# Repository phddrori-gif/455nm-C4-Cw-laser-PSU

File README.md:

# 455 nm 151 W Laser Array

## Overview
This repository documents the design, assembly, and testing of a 455 nm, 151 W diode laser array system built for high-power laser experimentation and materials research. The project combines optical, electrical, thermal, and safety engineering to create a controlled platform for evaluating laser performance and exploring laser-heated crystal growth.

## Project Objectives
- Achieve the full 151 W output of the diode array
- Explore laser-based growth of synthetic ruby
- Evaluate whether the system can be adapted for additional materials, including sapphire

## Current Status
The laser platform is operational in several core areas, with major progress completed in the safety, electrical, and mechanical subsystems. Remaining work is focused on characterization, documentation, and material-processing experiments.

## Safety Systems
Because this project involves a high-power 455 nm laser source, safety controls were treated as a primary design requirement.

Implemented safety features:
- OD8+ laser safety eyewear rated for 455 nm
- Hall-effect current sensing with ESP32-based monitoring
- Temperature-based automatic shutdown
- Emergency stop (E-stop)

## Mechanical and System Assembly
Completed design and integration work includes:
- 3D CAD model for the laser and circuit assembly
- Circuit design and schematic development
- PCB layout
- Custom lens holder
- Hybrid cooling system using both water cooling and forced-air cooling

## Electrical and Control Design
Completed electrical work:
- Tested PWM control and mechanical switch logic
- Verified full-wave rectifier suitability for 120 V AC input
- Integrated an IRM-05-3.3 power supply for the Teensy 4.0 controller
- Selected a 5.6 kOhm thermistor reference resistor based on a maximum expected operating temperature of 75 C

In progress:
- Fully label and reorganize the circuit diagram into clearly separated functional blocks

## Optical and Thermal Work
Completed:
- Selected a candidate focal length for the lens system (approximately +30 cm)

In progress:
- Determine the diode array's maximum allowable thermal load
- Measure and verify the optical power output of the diode array

## Materials and Crystal Growth Experiments
Completed:
- Acquired crucible for high-temperature material tests
- Acquired aluminum powder and chromium oxide for ruby experiments
- Planned work to be conducted in a fume hood

Planned:
- Acquire aluminum powder and iron oxide for sapphire experiments
- Evaluate the addition of titanium oxide for blue sapphire trials

## Next Steps
- Complete final circuit documentation
- Characterize thermal limits of the diode array
- Measure output power under controlled operating conditions
- Begin laser-heated ruby growth experiments
- Expand testing to additional materials if ruby trials are successful

## Resume Highlights
This project demonstrates experience in:
- High-power laser system integration
- Embedded monitoring and safety interlocks
- PCB and circuit design
- Thermal management
- Experimental hardware development
- Applied materials research

## Disclaimer
This repository documents work involving high-power laser equipment and high-temperature material processing. Testing should only be performed with proper protective equipment, controlled procedures, and appropriate lab safety infrastructure.

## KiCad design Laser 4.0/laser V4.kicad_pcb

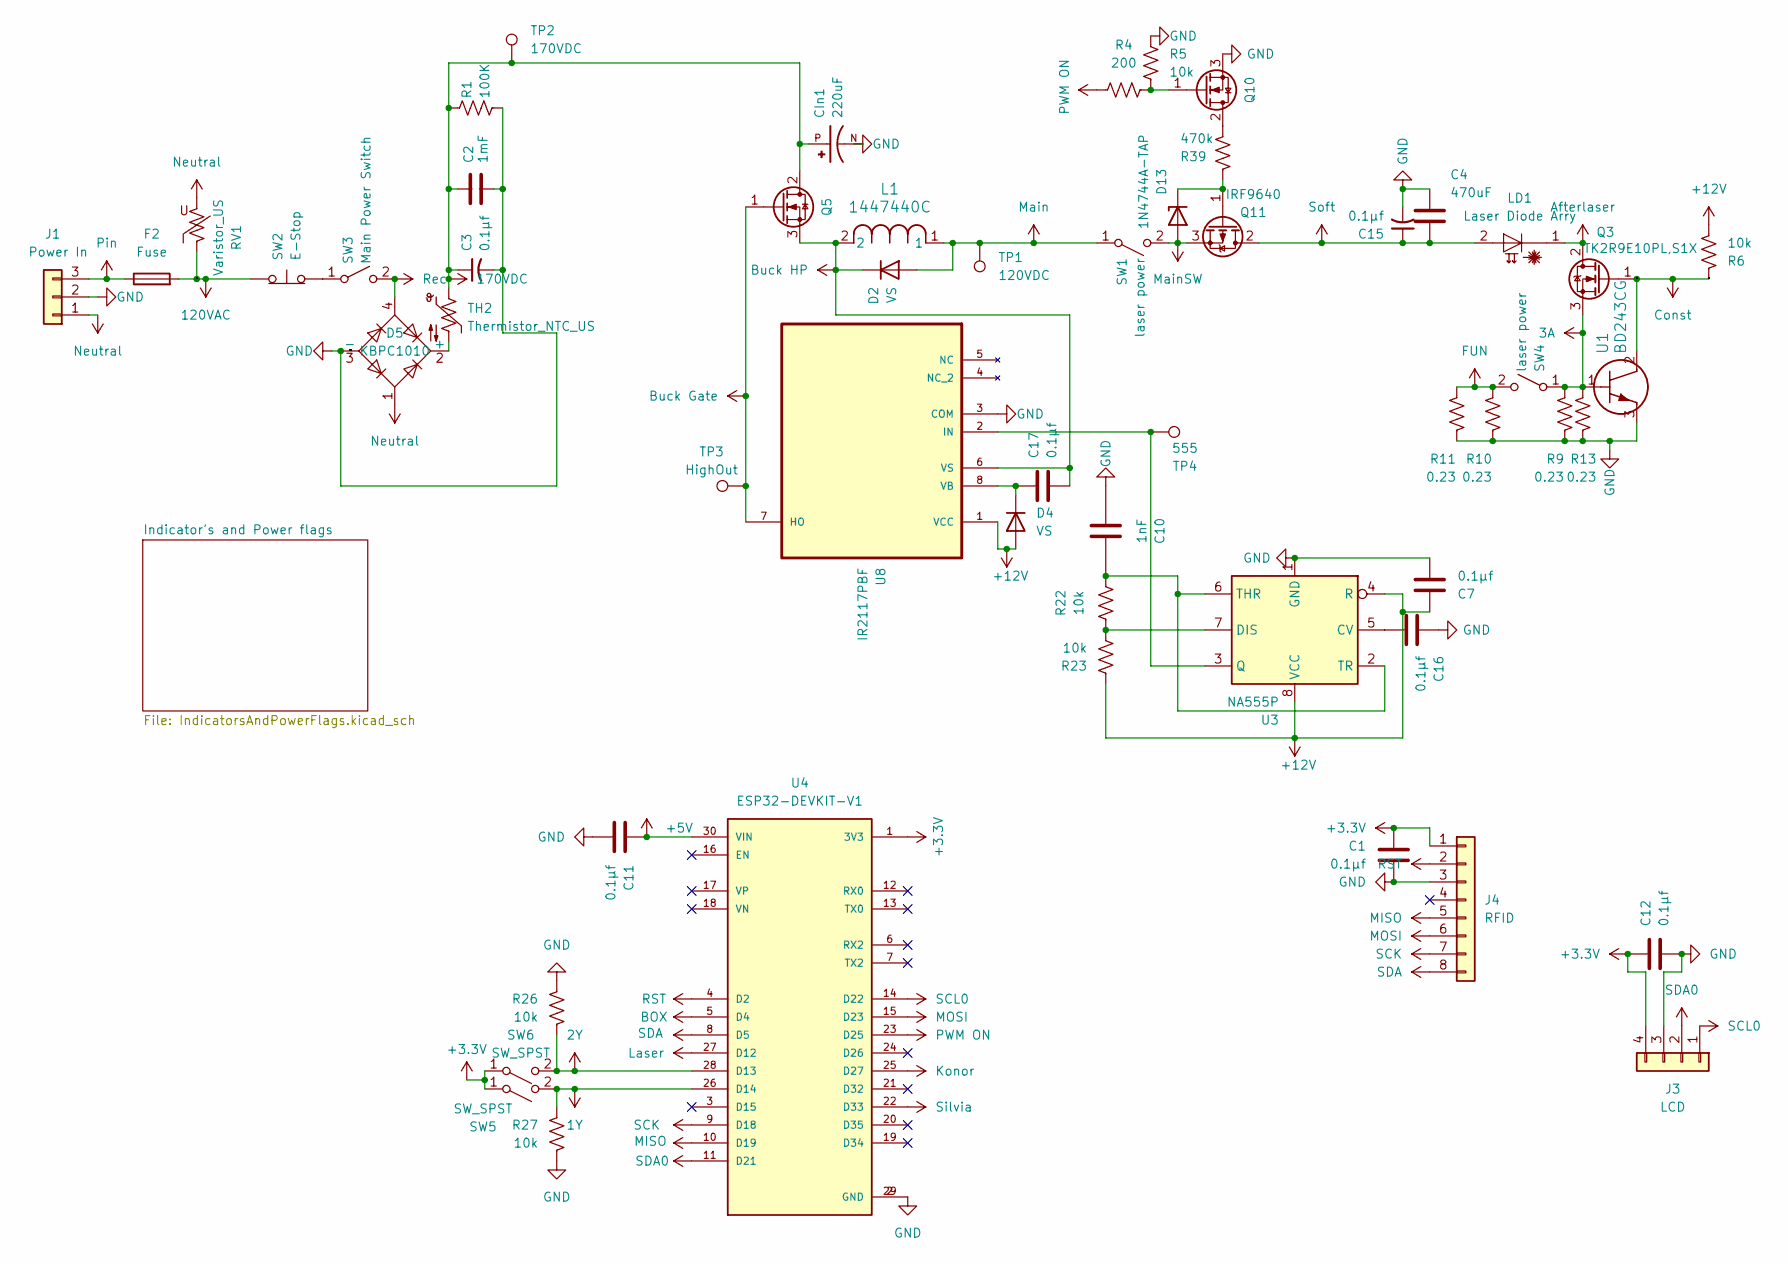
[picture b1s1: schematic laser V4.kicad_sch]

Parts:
C1, C7, C11, C12, C16, C17: 0.1µf; CP_Radial_D4.0mm_P2.00mm; Digikey 399-C320C104K5R5TA7305CT-ND
C2: 1mF; CP_Radial_D35.0mm_P10.00mm_SnapIn; Digikey 493-8541-ND
C3, C15: 0.1µf; CP_Radial_D4.0mm_P2.00mm; Digikey 399-3508-ND
C4: 470uF; CAPPRD500W60D1000H3150; Digikey 565-2971-ND
C10: 1nF; CP_Radial_D4.0mm_P2.00mm; Digikey 56-K102K15X7RF53H5G-ND
CIn1: 220uF; CAPPRD750W80D1600H3150; PARTREV 28-FEB-20; Digikey P13529-ND
D2, D4: VS; TO-220-2_Vertical; Digikey VS-HFA04TB60-M3GI-ND
D5: KBPC1010; Digikey 5272-KBPC1010-ND
D13: 1N4744A-TAP; D_DO-41_SOD81_P10.16mm_Horizontal; Digikey 1N4744A-TAPGICT-ND
F2: Fuse; Fuseholder_Clip-5x20mm_Littelfuse_100_Inline_P20.50x4.60mm_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; Digikey 486-4875-ND
J1: Power In; C14_thru hole
J3: LCD; FanPinHeader_1x04_P2.54mm_Vertical
J4: RFID; PinSocket_1x08_P2.54mm_Vertical
L1: 1447440C; 1447440C_MUR; Digikey 811-1332-ND
LD1: Laser Diode Arry; NUBM3D_LaserDiode_Pads
Q3: TK2R9E10PL,S1X; TO-220-3_Horizontal_TabUp; Digikey 264-TK2R9E10PL,S1X-ND
Q5, Q10: SIHP33N60E-GE3; TO-220-3_Horizontal_TabUp; Digikey 742-SIHP33N60E-GE3-ND
Q11: IRF9640; TO-220-3_Horizontal_TabUp; Digikey 742-IRF9640PBF-BE3-ND
R1: 100K; R_Axial_DIN0411_L9.9mm_D3.6mm_P12.70mm_Horizontal; Digikey A131429CT-ND
R4: 200; R_Axial_DIN0207_L6.3mm_D2.5mm_P10.16mm_Horizontal; Digikey RNF14FTD200RTR-ND
R5, R6, R22, R26, R27: 10k; R_Axial_DIN0207_L6.3mm_D2.5mm_P10.16mm_Horizontal; Digikey CF14JT10K0TR-ND
R9, R10, R11, R13: 0.23; R_Axial_Power_L20.0mm_W6.4mm_P25.40mm; Digikey A137272CT-ND
R23: 10k; R_Axial_DIN0207_L6.3mm_D2.5mm_P10.16mm_Horizontal; Digikey S3.3KQTR-ND
R39: 470k; R_Axial_DIN0207_L6.3mm_D2.5mm_P10.16mm_Horizontal
RV1: Varistor_US; VARRB750W81L1700T500H2250; DigiKey F4008-ND
SW1, SW4: laser power; TerminalBlock_WAGO_236-402_1x02_P5.00mm_45Degree; Digikey 708-3049-ND
SW2: E-Stop; TerminalBlock_WAGO_236-402_1x02_P5.00mm_45Degree
SW3: Main Power Switch; TerminalBlock_WAGO_236-402_1x02_P5.00mm_45Degree; Digikey 708-3049-ND
SW5, SW6: SW_SPST; PinHeader_1x02_P2.54mm_Vertical
TH2: Thermistor_NTC_US; RV_Disc_D21.5mm_W7.5mm_P10mm; Digikey 570-MS3220010-ND
TP1: 120VDC; TestPoint_Plated_Hole_D2.0mm
TP2: 170VDC; TestPoint_Plated_Hole_D2.0mm
TP3: HighOut; TestPoint_Plated_Hole_D2.0mm
TP4: 555; TestPoint_Plated_Hole_D2.0mm
U1: BD243CG; TO-220-3_Horizontal_TabUp; Digikey BD243CGOS-ND
U3: NA555P; DIP-8_W7.62mm; Digikey 296-21753-5-ND
U4: ESP32-DEVKIT-V1; MODULE_ESP32_DEVKIT_V1; PARTREV N/A
U8: IR2117PBF; DIP254P762X533-8; MPN IR2117PBF

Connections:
1Y: R27.1, SW5.2 (B), U4.26 (D14); also elsewhere on the board
2Y: R26.2, SW6.2 (B), U4.28 (D13); also elsewhere on the board
3A: Q3.3 (S), R9.1, R13.1, SW4.1 (A), U1.1
120VAC: F2.2, RV1.1, SW2.1 (A)
170VDC: C2.1, C3.1, CIn1.P, D5.2 (+), Q5.2 (D), R1.1, TH2.1, TH2.2, TP2.1; also elsewhere on the board
+3.3V: C1.1, C12.1, J3.4, J4.1, SW5.1 (A), SW6.1 (A), U4.1 (3V3); also elsewhere on the board
+5V: C11.1, U4.30 (VIN); also elsewhere on the board
+12V: C7.1, D4.2 (A), R6.2, R23.1, U3.4 (R), U3.8 (VCC), U8.1 (VCC); also elsewhere on the board
Afterlaser: LD1.1 (C), Q3.2 (D)
BOX: U4.5 (D4)
Buck Gate: Q5.1 (G), TP3.1, U8.7 (HO)
Buck HP: C17.2, D2.1 (K), L1.2, Q5.3 (S), U8.6 (VS)
Const: Q3.1 (G), R6.1, U1.2
FUN: R10.1, R11.1, SW4.2 (B); also elsewhere on the board
GND: C1.2, C2.2, C3.2, C4.1, C7.2, C10.2, C11.2, C12.2, C15.2, C16.1, CIn1.N, D5.3 (-), J1.2, J3.3, J4.3, Q10.3 (S), R1.2, R5.1, R9.2, R10.2, R11.2, R13.2, R26.1, R27.2, U1.3, U3.1 (GND), U4.2 (GND), U4.29 (GND), U8.3 (COM); also elsewhere on the board
Konor: U4.25 (D27); also elsewhere on the board
Laser: U4.27 (D12); also elsewhere on the board
MISO: J4.5, U4.10 (D19)
MOSI: J4.6, U4.15 (D23)
Main: D2.2 (A), L1.1, SW1.1 (A), TP1.1
MainSW: D13.2 (A), Q11.3 (S), SW1.2 (B)
unnamed: C17.1, D4.1 (K), U8.8 (VB)
unnamed: D13.1 (K), Q11.1 (G), R39.1
unnamed: Q10.2 (D), R39.2
unnamed: Q10.1 (G), R4.2, R5.2
unnamed: SW2.2 (B), SW3.1 (A)
unnamed: C16.2, U3.5 (CV)
unnamed: R22.2, R23.2, U3.7 (DIS)
unnamed: TP4.1, U3.3 (Q), U8.2 (IN)
unnamed: C10.1, R22.1, U3.2 (TR), U3.6 (THR)
Neutral: D5.1, J1.1, RV1.2; also elsewhere on the board
PWM ON: R4.1, U4.23 (D25)
Pin: F2.1, J1.3; also elsewhere on the board
RST: J4.2, U4.4 (D2)
Rec: D5.4, SW3.2 (B)
SCK: J4.7, U4.9 (D18)
SCL0: J3.1, U4.14 (D22)
SDA: J4.8, U4.8 (D5)
SDA0: J3.2, U4.11 (D21)
Silvia: U4.22 (D33); also elsewhere on the board
Soft: C4.2, C15.1, LD1.2 (A), Q11.2 (D)

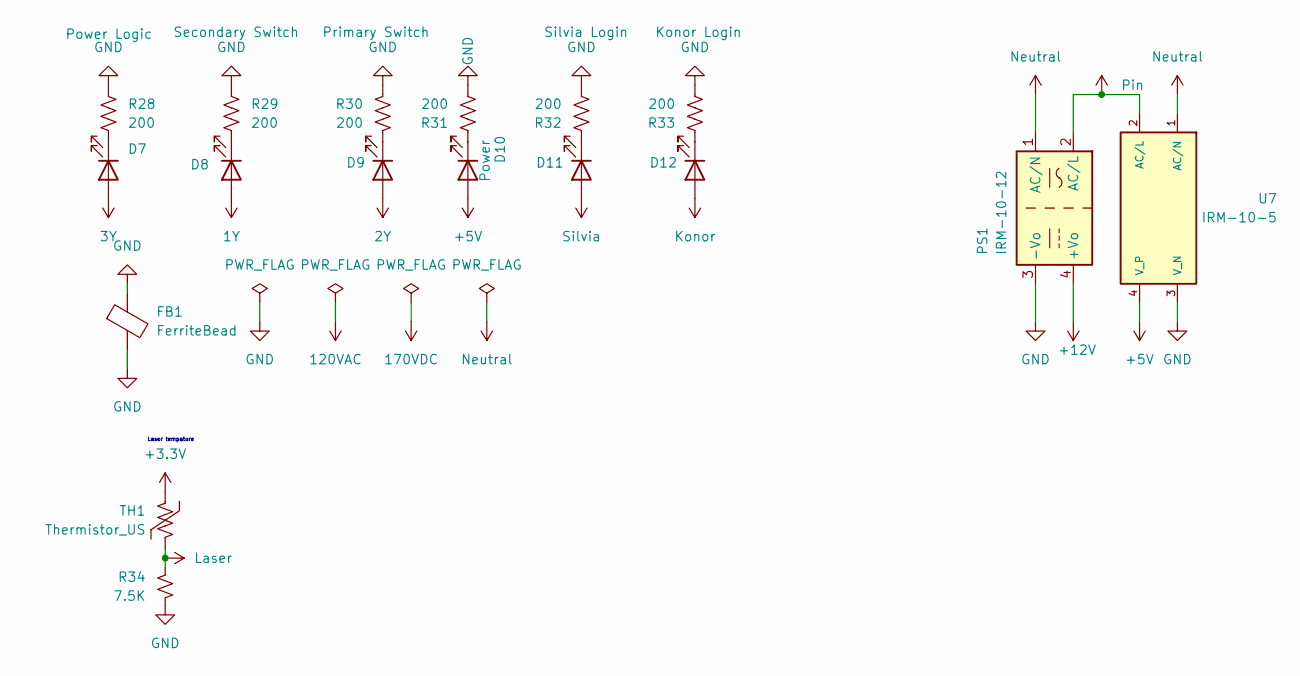
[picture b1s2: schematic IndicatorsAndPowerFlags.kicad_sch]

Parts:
D7: Power Logic; LED_D5.0mm; Digikey 732-5016-ND
D8: Secondary Switch; LED_D5.0mm; Digikey 732-5016-ND
D9: Primary Switch; LED_D5.0mm; Digikey 732-5016-ND
D10: Power; LED_D5.0mm; Digikey 732-5016-ND
D11: Silvia Login; LED_D5.0mm; Digikey 732-5016-ND
D12: Konor Login; LED_D5.0mm; Digikey 732-5016-ND
FB1: FerriteBead; R_Axial_DIN0207_L6.3mm_D2.5mm_P7.62mm_Horizontal; Digikey 1934-1476-2-ND
PS1: IRM-10-12; Converter_ACDC_MeanWell_IRM-10-xx_THT; Digikey 1866-3028-ND
R28, R29, R30, R31, R32, R33: 200; R_Axial_DIN0207_L6.3mm_D2.5mm_P10.16mm_Horizontal; Digikey RNF14FTD200RTR-ND
R34: 7.5K; R_Axial_DIN0207_L6.3mm_D2.5mm_P10.16mm_Horizontal
TH1: Thermistor_US; PinHeader_1x02_P2.54mm_Vertical; Digikey 317-1258-ND
U7: IRM-10-5; CONV_IRM-10-5; Digikey 1866-3032-ND

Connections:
1Y: D8.2 (A); also elsewhere on the board
2Y: D9.2 (A); also elsewhere on the board
3Y: D7.2 (A)
+3.3V: TH1.1; also elsewhere on the board
+5V: D10.2 (A), U7.4 (V_P); also elsewhere on the board
+12V: PS1.4 (+Vo); also elsewhere on the board
GND: FB1.1, FB1.2, PS1.3 (-Vo), R28.1, R29.2, R30.1, R31.2, R32.2, R33.2, R34.1, U7.3 (V_N); also elsewhere on the board
Konor: D12.2 (A); also elsewhere on the board
Laser: R34.2, TH1.2; also elsewhere on the board
unnamed: D7.1 (K), R28.2
unnamed: D8.1 (K), R29.1
unnamed: D9.1 (K), R30.2
unnamed: D10.1 (K), R31.1
unnamed: D11.1 (K), R32.1
unnamed: D12.1 (K), R33.1
Neutral: PS1.1 (AC/N), U7.1 (AC/N); also elsewhere on the board
Pin: PS1.2 (AC/L), U7.2 (AC/L); also elsewhere on the board
Silvia: D11.2 (A); also elsewhere on the board

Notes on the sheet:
Laser tempature

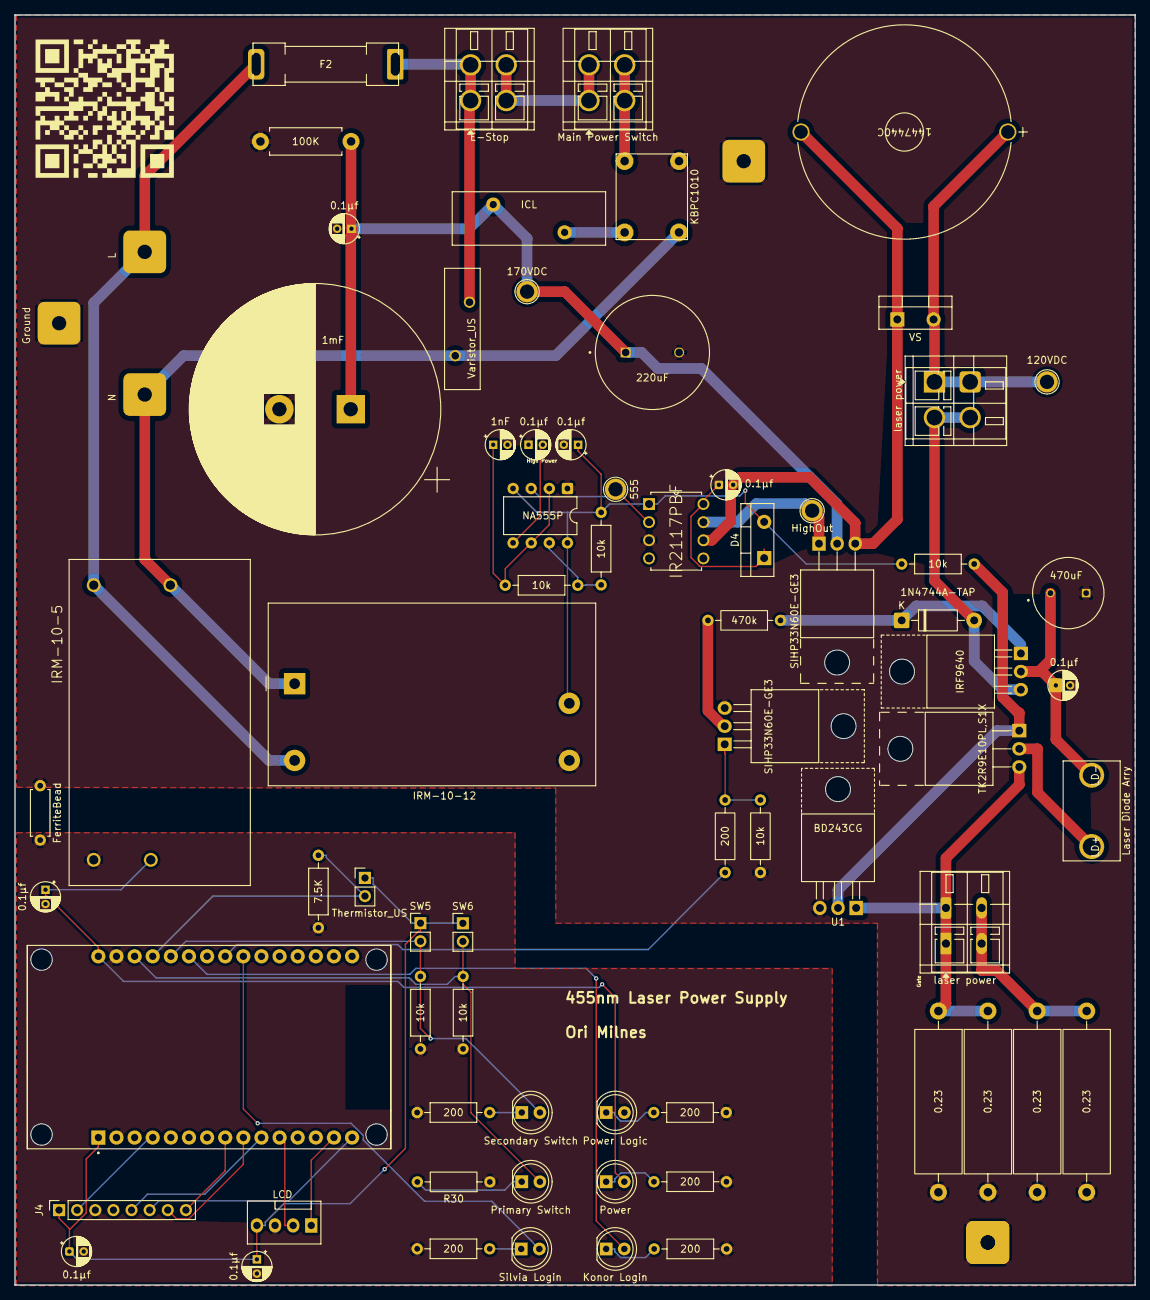
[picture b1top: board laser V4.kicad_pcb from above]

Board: 2 copper layers, 157.0 x 178.0 mm, 73 parts (0 on the bottom side), 46 nets.

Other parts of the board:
0.23, 0.23#2: 0.23; R_Axial_Power_L20.0mm_W6.4mm_P25.40mm
G1: LOGO
ICL: Thermistor_NTC_US; RV_Disc_D21.5mm_W7.5mm_P10mm

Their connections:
170VDC: ICL.1, ICL.2; also elsewhere on the board
FUN: 0.23.1, 0.23#2.1; also elsewhere on the board
GND: 0.23.2, 0.23#2.2; also elsewhere on the board

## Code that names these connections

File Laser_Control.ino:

#include <Wire.h>
#include <SPI.h>
#include <MFRC522.h>
#include <LiquidCrystal_I2C.h>
#include <math.h>
#include <Watchdog_t4.h>

WDT_T4<WDT1> wdt;

// RFID RC522
#define RST_PIN 9
#define SS_PIN 10
MFRC522 mfrc522(SS_PIN, RST_PIN);

// LCD I2C
LiquidCrystal_I2C lcd(0x27, 16, 2);

// Known UIDs
const byte UID_A[] = { 0x73, 0xD6, 0xEE, 0xAE };  // KONOR
const byte UID_B[] = { 0x53, 0x77, 0xAB, 0x98 };  // SILVIA
const byte UID_A_LEN = sizeof(UID_A);
const byte UID_B_LEN = sizeof(UID_B);

// Pins
const int THERMISTOR_LASER_PIN  = A0;  // pin 14
const int THERMISTOR_MOSFET_PIN = A3;  // pin 17
const int VOLTAGE1_PIN   = A1;  // pin 15
const int VOLTAGE2_PIN   = A2;  // pin 16
const int CURRENT_PIN    = A8;  // pin 22
const int PWM_LASER_PIN  = 23;
const int PWM_ON_PIN     = 8;
const int KONOR_LED_PIN  = 6;
const int SILVIA_LED_PIN = 7;

// Constants
const float ADC_REF = 3.3;
const int ADC_RES = 4095;
const float SHUNT_RESISTANCE = 0.1;
const float VOLT_DIV_RATIO_1 = 57.0;
const float VOLT_DIV_RATIO_2 = 37.0;

// System State
bool isA_loggedIn = false;
bool isB_loggedIn = false;
bool isLocked = false;
bool inCooldown = false;
int unknownScanCount = 0;
int pwmLaserValue = 255;  // default 100%

// Override
bool overrideMode = false;
unsigned long overrideStartTime = 0;
const unsigned long overrideDuration = 60000;
unsigned long lastUIDScanTime = 0;
const unsigned long overrideScanWindow = 3000;
byte lastUID[10];
byte lastUIDLen = 0;

// Timing
unsigned long lastVoltageSwitch = 0;
unsigned long lastDisplayUpdate = 0;
unsigned long cooldownStart = 0;
const unsigned long voltageSwitchInterval = 5000;
const unsigned long displayInterval = 200;
const unsigned long cooldownDuration = 60000;
bool showVoltage1 = true;

// Soft start
unsigned long softStartStartTime = 0;
const unsigned long softStartDuration = 5000;  // 5 seconds

void setup() {
  Serial.begin(115200);
  analogReadResolution(12);
  analogReadAveraging(8);
  pinMode(PWM_LASER_PIN, OUTPUT);
  pinMode(PWM_ON_PIN, OUTPUT);
  pinMode(KONOR_LED_PIN, OUTPUT);
  pinMode(SILVIA_LED_PIN, OUTPUT);
  analogWrite(PWM_LASER_PIN, 0);
  analogWrite(PWM_ON_PIN, 0);

  WDT_timings_t config = {
    .trigger = 8000,
    .timeout = 16000,
    .callback = nullptr
  };
  wdt.begin(config);

  lcd.init();
  lcd.backlight();
  lcd.setCursor(0, 0);
  lcd.print("LCD OK...");
  delay(500);

  SPI.begin();
  mfrc522.PCD_Init();
  delay(100);
  lcd.clear();
  lcd.print("RFID Ready");
  delay(1000);
  lcd.clear();
}

void loop() {
  wdt.feed();

  static int lastPwmOnValue = -1;
  static int lastLaserPwmValue = -1;
  static bool lastPwmOn = false;

  digitalWrite(KONOR_LED_PIN, isA_loggedIn);
  digitalWrite(SILVIA_LED_PIN, isB_loggedIn);

  float tempC = readTemperature(THERMISTOR_LASER_PIN);
  if ((tempC >= 60.0 || tempC > 150.0) && !inCooldown) enterCooldown("TEMP ERROR");
  if (inCooldown) { handleCooldown(); return; }

  if (Serial.available()) {
    int input = Serial.parseInt();
    if (input >= 0 && input <= 255) {
      pwmLaserValue = input;
    }
  }

  // RFID logic
  if (mfrc522.PICC_IsNewCardPresent() && mfrc522.PICC_ReadCardSerial()) {
    byte* uid = mfrc522.uid.uidByte;
    byte uidLen = mfrc522.uid.size;
    unsigned long now = millis();

    if (compareUID(uid, uidLen, UID_A, UID_A_LEN)) {
      if (lastUIDLen == UID_A_LEN && compareUID(uid, uidLen, lastUID, lastUIDLen)) {
        if (now - lastUIDScanTime <= overrideScanWindow) {
          overrideMode = true;
          overrideStartTime = now;
          softStartStartTime = now;
          lcd.clear();
          lcd.setCursor(0, 0);
          lcd.print("OVERRIDE MODE");
          delay(1000);
          lcd.clear();
        }
      }
      memcpy(lastUID, uid, uidLen);
      lastUIDLen = uidLen;
      lastUIDScanTime = now;
    }

    if (compareUID(uid, uidLen, UID_A, UID_A_LEN)) {
      isA_loggedIn = !isA_loggedIn;
      unknownScanCount = 0;
    } else if (compareUID(uid, uidLen, UID_B, UID_B_LEN)) {
      if (!isLocked) {
        isB_loggedIn = !isB_loggedIn;
        unknownScanCount = 0;
      }
    } else {
      unknownScanCount++;
      if (unknownScanCount >= 2) {
        isA_loggedIn = false;
        isB_loggedIn = false;
        isLocked = true;
      }
    }

    mfrc522.PICC_HaltA();
  }

  if (overrideMode && millis() - overrideStartTime > overrideDuration) {
    overrideMode = false;
  }

  float currentVoltage = analogRead(CURRENT_PIN) * (ADC_REF / ADC_RES);
  float currentAmps = currentVoltage / SHUNT_RESISTANCE;
  float voltage1 = analogRead(VOLTAGE1_PIN) * (ADC_REF / ADC_RES) * VOLT_DIV_RATIO_1;
  float voltage2 = analogRead(VOLTAGE2_PIN) * (ADC_REF / ADC_RES) * VOLT_DIV_RATIO_2;

  bool pwmOn = ((isA_loggedIn && isB_loggedIn) || overrideMode) && !isLocked;

  // Detect rising edge for soft start
  if (pwmOn && !lastPwmOn) {
    softStartStartTime = millis();
  }
  lastPwmOn = pwmOn;

  // Soft-start PWM (pin 8)
  int pwmOnValue = 0;
  if (pwmOn) {
    unsigned long elapsed = millis() - softStartStartTime;
    pwmOnValue = (elapsed >= softStartDuration) ? 255 : map(elapsed, 0, softStartDuration, 0, 255);
  } else {
    pwmOnValue = 0;
  }
  if (pwmOnValue != lastPwmOnValue) {
    analogWrite(PWM_ON_PIN, pwmOnValue);
    lastPwmOnValue = pwmOnValue;
  }

  // Laser PWM (pin 23)
  int laserPwmValue = (pwmOn ? pwmLaserValue : 0);
  if (laserPwmValue != lastLaserPwmValue) {
    analogWrite(PWM_LASER_PIN, laserPwmValue);
    lastLaserPwmValue = laserPwmValue;
  }

  // Display control
  if (millis() - lastVoltageSwitch > voltageSwitchInterval) {
    showVoltage1 = !showVoltage1;
    lastVoltageSwitch = millis();
  }

  if (millis() - lastDisplayUpdate >= displayInterval) {
    lcd.setCursor(0, 0);

    if (overrideMode) {
      lcd.print("OVERRIDE MODE   ");
      lcd.setCursor(0, 1);
      unsigned long remaining = (overrideDuration - (millis() - overrideStartTime)) / 1000;
      lcd.print("Time Left: ");
      if (remaining < 10) lcd.print(" ");
      lcd.print(remaining);
      lcd.print("s   ");
    } else if (pwmOn) {
      lcd.print("POWER:ON  PWM:");
      lcd.print((int)(pwmLaserValue * 100 / 255));
      lcd.print("% ");
      lcd.setCursor(0, 1);
      float displayV = showVoltage1 ? voltage1 : voltage2;
      lcd.print(showVoltage1 ? "V1:" : "V2:");
      lcd.print((int)displayV);
      if (displayV < 100) lcd.print(" ");
      if (displayV < 10) lcd.print(" ");
      lcd.print(" ");
      printFixed(lcd, currentAmps, 3, 1);
      lcd.print("A");
    } else {
      lcd.print("Silvia:");
      lcd.print(isB_loggedIn ? "Y " : "N ");
      lcd.print("Konor:");
      lcd.print(isA_loggedIn ? "Y" : "N ");
      lcd.print("   ");
      lcd.setCursor(0, 1);
      float displayV = showVoltage1 ? voltage1 : voltage2;
      lcd.print(showVoltage1 ? "V1:" : "V2:");
      lcd.print((int)displayV);
      if (displayV < 100) lcd.print(" ");
      if (displayV < 10) lcd.print(" ");
      lcd.print(" ");
      printFixed(lcd, currentAmps, 3, 1);
      lcd.print("A");
    }

    lastDisplayUpdate = millis();
  }
}

float readTemperature(int pin) {
  const float Vcc = 3.3;
  const float R_FIXED = 10000.0;
  const float BETA = 3950.0;
  const float T0 = 298.15;
  int raw = analogRead(pin);
  if (raw < 5 || raw > 4090) return 999.0;
  float Vout = raw * (Vcc / ADC_RES);
  float R_therm = R_FIXED * ((Vcc / Vout) - 1.0);
  float tempK = 1.0 / (log(R_therm / R_FIXED) / BETA + (1.0 / T0));
  return tempK - 273.15;
}

bool compareUID(const byte *uid1, byte len1, const byte *uid2, byte len2) {
  if (len1 != len2) return false;
  for (byte i = 0; i < len1; i++) {
    if (uid1[i] != uid2[i]) return false;
  }
  return true;
}

void enterCooldown(const char* reason) {
  isA_loggedIn = false;
  isB_loggedIn = false;
  isLocked = true;
  inCooldown = true;
  overrideMode = false;
  analogWrite(PWM_LASER_PIN, 0);
  analogWrite(PWM_ON_PIN, 0);
  lcd.clear();
  lcd.setCursor(0, 0);
  lcd.print(reason);
  cooldownStart = millis();
}

void handleCooldown() {
  unsigned long elapsed = millis() - cooldownStart;
  unsigned long remaining = (cooldownDuration - elapsed) / 1000;
  lcd.setCursor(0, 1);
  lcd.print("Cooldown: ");
  if (remaining < 10) lcd.print(" ");
  lcd.print(remaining);
  lcd.print("s   ");
  if (elapsed >= cooldownDuration) {
    inCooldown = false;
    isLocked = false;
    lcd.clear();
    lcd.print("Cooldown done");
    delay(1000);
    lcd.clear();
  }
}

void printFixed(LiquidCrystal_I2C &lcd, float value, int digits, int decimals) {
  char buffer[8];
  dtostrf(value, digits + decimals + 1, decimals, buffer);
  lcd.print(buffer);
}

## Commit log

2026-04-08 naming clarification
2026-04-08 added solidwork files
